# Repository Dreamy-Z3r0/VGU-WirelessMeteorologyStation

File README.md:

# VGU-WirelessMeteorologyStation

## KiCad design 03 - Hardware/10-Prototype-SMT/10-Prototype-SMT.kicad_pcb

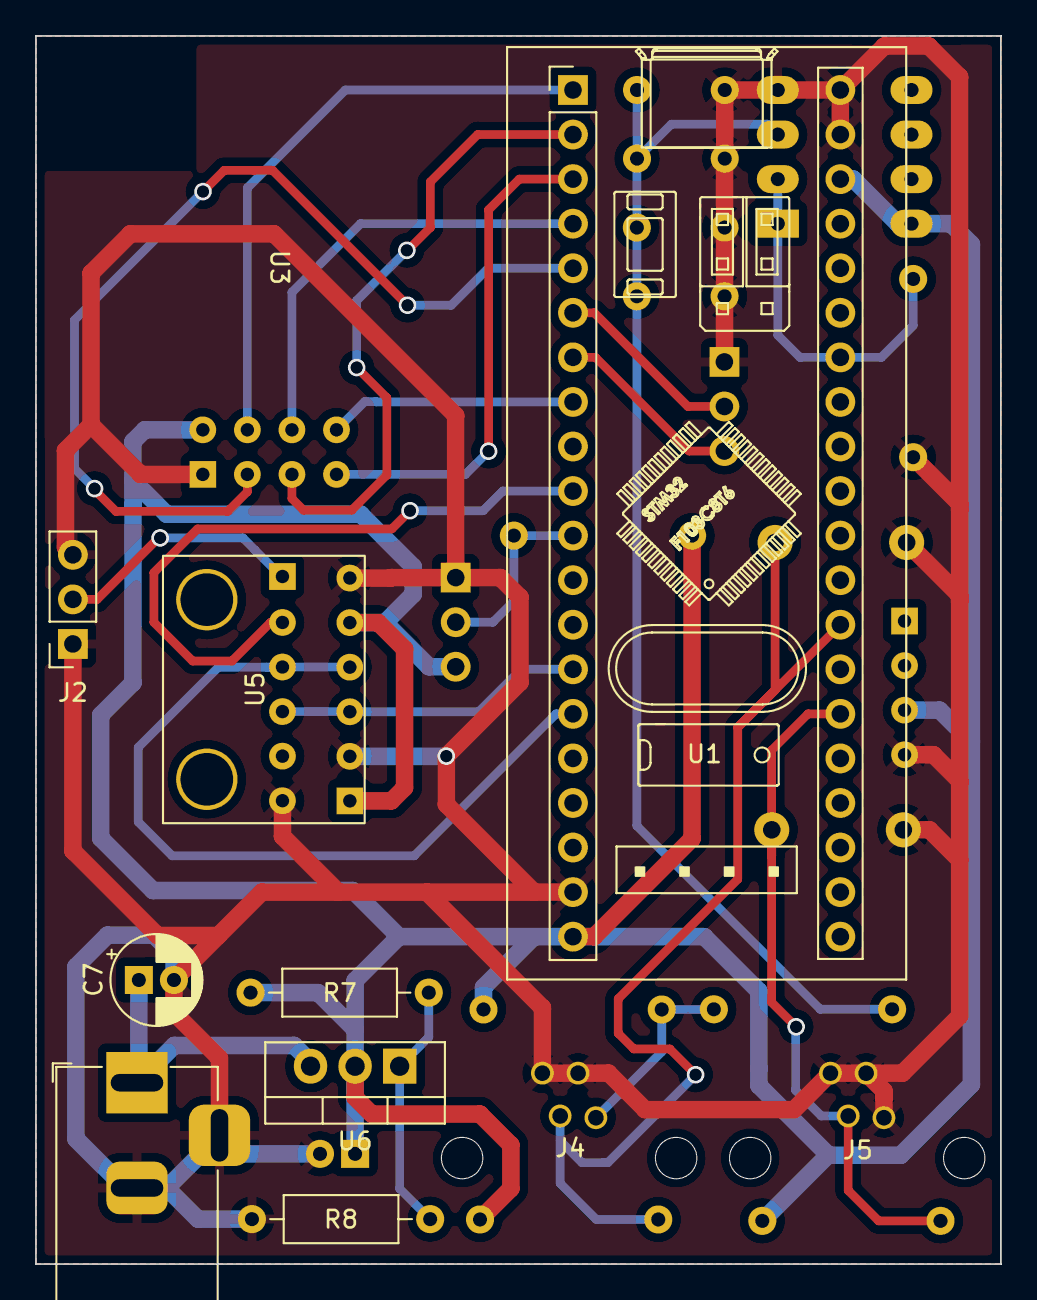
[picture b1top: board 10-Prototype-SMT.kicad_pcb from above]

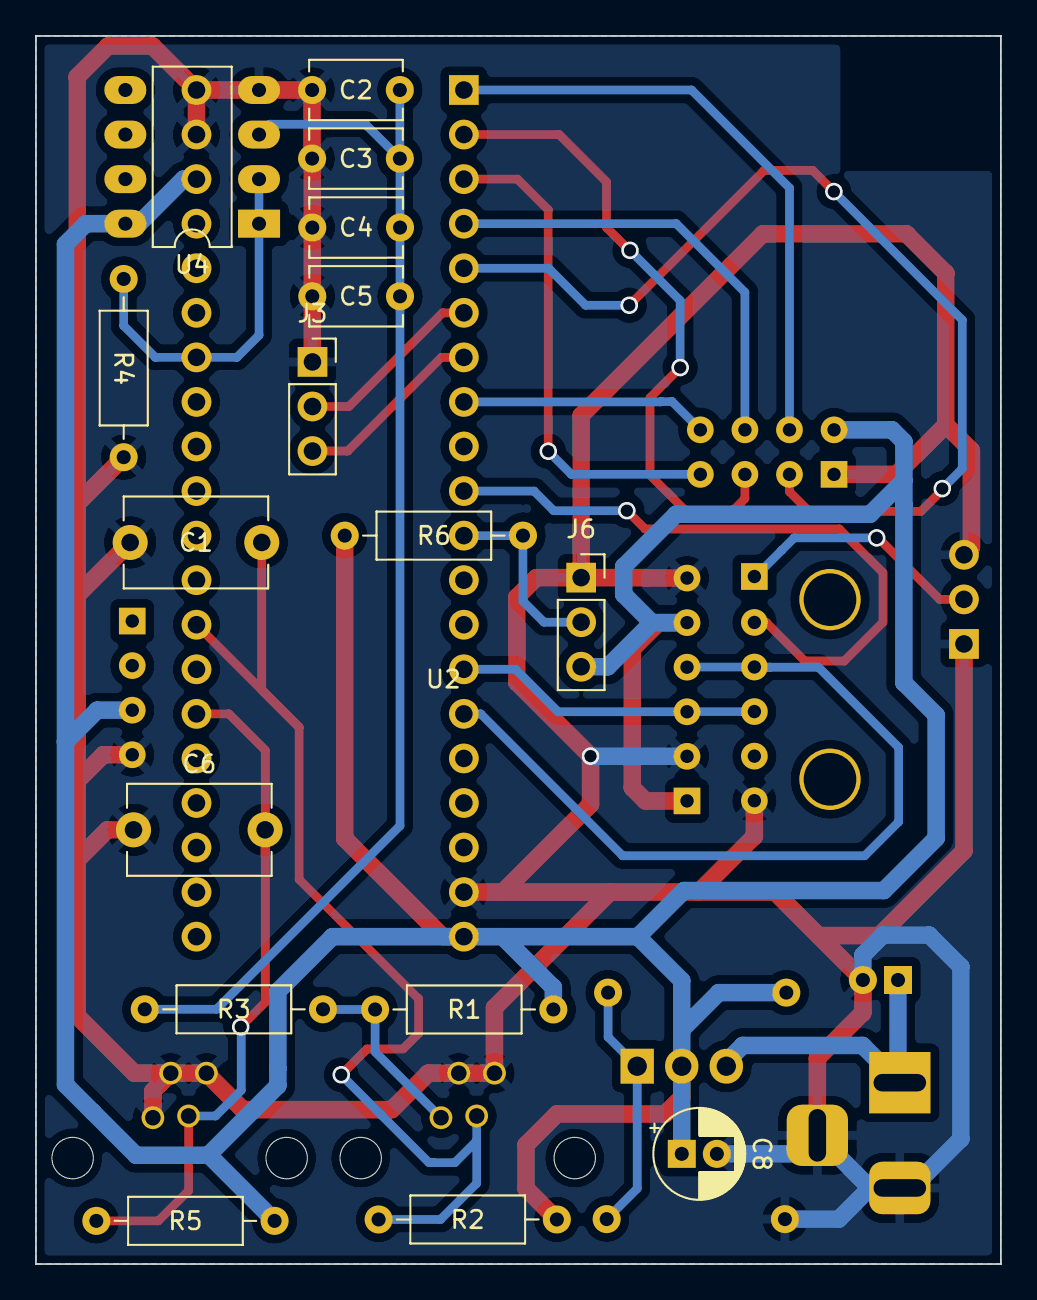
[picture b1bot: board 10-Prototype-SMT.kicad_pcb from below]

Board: 2 copper layers, 55.0 x 70.0 mm, 28 parts (17 on the bottom side), 22 nets.

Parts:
C1, C6: 68n; C_Disc_D8.0mm_W5.0mm_P7.50mm
C2: 10n; C_Disc_D5.1mm_W3.2mm_P5.00mm
C3: 4.7n; C_Disc_D5.1mm_W3.2mm_P5.00mm
C4: 3.3n; C_Disc_D5.1mm_W3.2mm_P5.00mm
C5: 2.2n; C_Disc_D5.1mm_W3.2mm_P5.00mm
C7: 0.1u; CP_Radial_D5.0mm_P2.00mm
C8: 1u; CP_Radial_D5.0mm_P2.00mm
J1: Barrel_Jack; BarrelJack_Horizontal
J2, J3, J6: Conn_01x03_Male; PinSocket_1x03_P2.54mm_Vertical
J4, J5: 4P4C
R1: 3k; R_Axial_DIN0207_L6.3mm_D2.5mm_P10.16mm_Horizontal
R2, R5: 33k; R_Axial_DIN0207_L6.3mm_D2.5mm_P10.16mm_Horizontal
R3: 680; R_Axial_DIN0207_L6.3mm_D2.5mm_P10.16mm_Horizontal
R4: 3.3k; R_Axial_DIN0207_L6.3mm_D2.5mm_P10.16mm_Horizontal
R6: 4.7k; R_Axial_DIN0207_L6.3mm_D2.5mm_P10.16mm_Horizontal
R7: 240; R_Axial_DIN0207_L6.3mm_D2.5mm_P10.16mm_Horizontal
R8: 390; R_Axial_DIN0207_L6.3mm_D2.5mm_P10.16mm_Horizontal
U1: YAAJ_BluePill; YAAJ_BluePill_1
U2: DS3231_Full_Pinout; DS3231_Module_FullSize
U3: SX1278_Minimal
U4: MCP6002-xP; DIP-8_W7.62mm_LongPads
U5: BME280_I2C_New_LK888; BME280_I2C_Small
U6: LM317_TO-220; TO-220-3_Vertical

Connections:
+3V3: C8.1, J6.3, R1.1, R2.1, R5.1, R6.1, R7.2, U1.20 (3V3), U1.38 (3V3), U2.3 (VCC), U3.2 (VCC), U4.8 (V+), U5.1 (VCC), U6.2 (VO)
/32768Hz out: J2.2, U2.5 (32K)
/Passive LPF: C2.1, C3.1, C4.1, C5.1, R3.2, U4.3 (+)
/V_adj: R7.1, R8.1, U6.1 (ADJ)
Anemometer: C1.2, J4.3, R2.2, U1.28 (PA3)
DS18B20: J6.2, R6.2, U1.11 (PB3)
GND: C1.1, C2.2, C3.2, C4.2, C5.2, C6.1, C7.2, C8.2, J1.2, J1.3, J2.1, J2.3, J3.1, J4.1, J4.2, J5.1, J5.2, J5.4, J6.1, R4.1, R8.2, U1.19 (GND), U1.39 (GND), U1.40 (GND), U2.4 (GND), U2.10 (GND), U3.1 (GND), U4.4 (V-), U5.2 (GND), U5.5 (ADDR)
I2C_CLK: U1.14 (PB6), U2.7 (SCL), U5.3 (SCL)
I2C_SDA: U1.15 (PB7), U2.8 (SDA), U5.4 (SDA)
LoRa_DIO0: U1.8 (PA11), U3.8 (DIO0)
LoRa_MISO: U1.3 (PB14), U3.7 (MISO)
LoRa_MOSI: U1.4 (PB15), U3.6 (MOSI)
LoRa_NCSS: U1.1 (PB12), U3.4 (NCSS)
LoRa_Reset: U1.5 (PA8), U3.3 (RST)
LoRa_SCLK: U1.2 (PB13), U3.5 (SCLK)
RTC_ALARM: U1.10 (PA15), U2.6 (SQW)
Rain_Gauge: C6.2, J5.3, R5.2, U1.26 (PA1)
UART_RX: J3.3, U1.7 (PA10)
UART_TX: J3.2, U1.6 (PA9)
VCC: C7.1, J1.1, U6.3 (VI)
WindVane_raw: J4.4, R1.2, R3.1
Wind_Vane: R4.2, U1.34 (PB1), U4.1, U4.2 (-)

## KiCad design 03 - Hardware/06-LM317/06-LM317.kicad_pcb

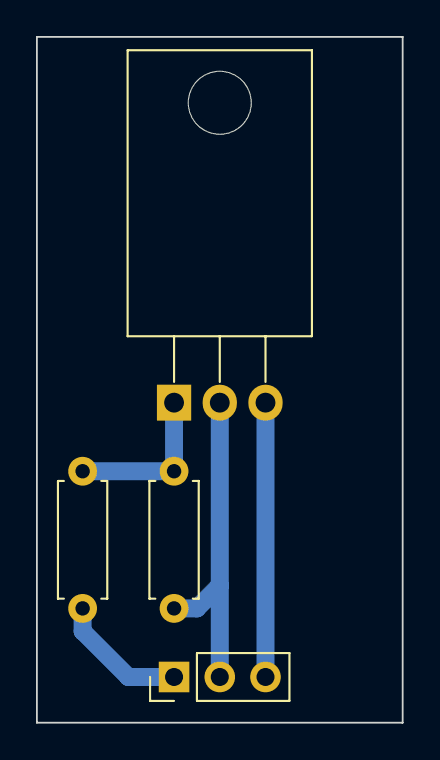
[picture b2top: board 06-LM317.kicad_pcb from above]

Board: 2 copper layers, 20.3 x 38.1 mm, 4 parts (0 on the bottom side), 4 nets.

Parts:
J1: Conn_01x03_Male; PinHeader_1x03_P2.54mm_Vertical
R1: 240; R_Axial_DIN0207_L6.3mm_D2.5mm_P7.62mm_Horizontal
R2: 390; R_Axial_DIN0207_L6.3mm_D2.5mm_P7.62mm_Horizontal
U1: LM317_TO-220; TO-220-3_Horizontal_TabDown

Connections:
/ADJ: R1.2, R2.1, U1.1 (ADJ)
GND: J1.1, R2.2
VIN: J1.3, U1.3 (VI)
VOUT: J1.2, R1.1, U1.2 (VO)

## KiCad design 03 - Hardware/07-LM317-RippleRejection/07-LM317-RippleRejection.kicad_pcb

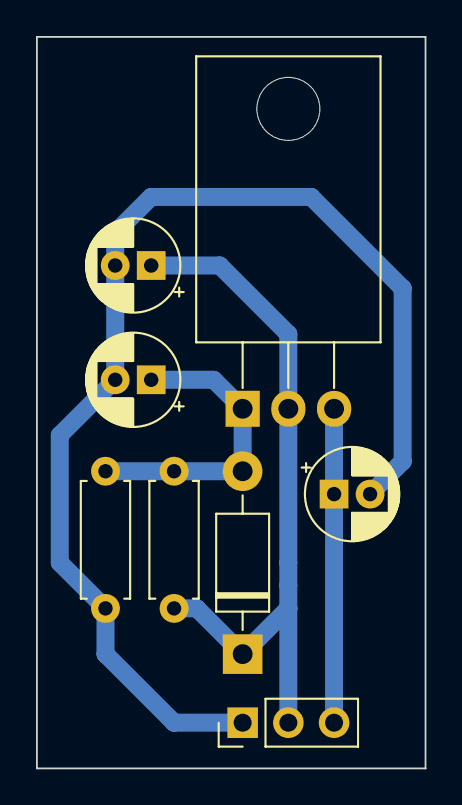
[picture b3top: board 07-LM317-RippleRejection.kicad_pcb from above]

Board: 2 copper layers, 21.6 x 40.6 mm, 8 parts (0 on the bottom side), 4 nets.

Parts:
C1: 0.1u; CP_Radial_D5.0mm_P2.00mm
C2: 10u; CP_Radial_D5.0mm_P2.00mm
C3: 1u; CP_Radial_D5.0mm_P2.00mm
D1: 1N4007; D_DO-41_SOD81_P10.16mm_Horizontal
J1: Conn_01x03_Male; PinHeader_1x03_P2.54mm_Vertical
R1: 240; R_Axial_DIN0207_L6.3mm_D2.5mm_P7.62mm_Horizontal
R2: 390; R_Axial_DIN0207_L6.3mm_D2.5mm_P7.62mm_Horizontal
U1: LM317_TO-220; TO-220-3_Horizontal_TabDown

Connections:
/ADJ: C2.1, D1.2 (A), R1.2, R2.1, U1.1 (ADJ)
GND: C1.2, C2.2, C3.2, J1.1, R2.2
VIN: C1.1, J1.3, U1.3 (VI)
VOUT: C3.1, D1.1 (K), J1.2, R1.1, U1.2 (VO)

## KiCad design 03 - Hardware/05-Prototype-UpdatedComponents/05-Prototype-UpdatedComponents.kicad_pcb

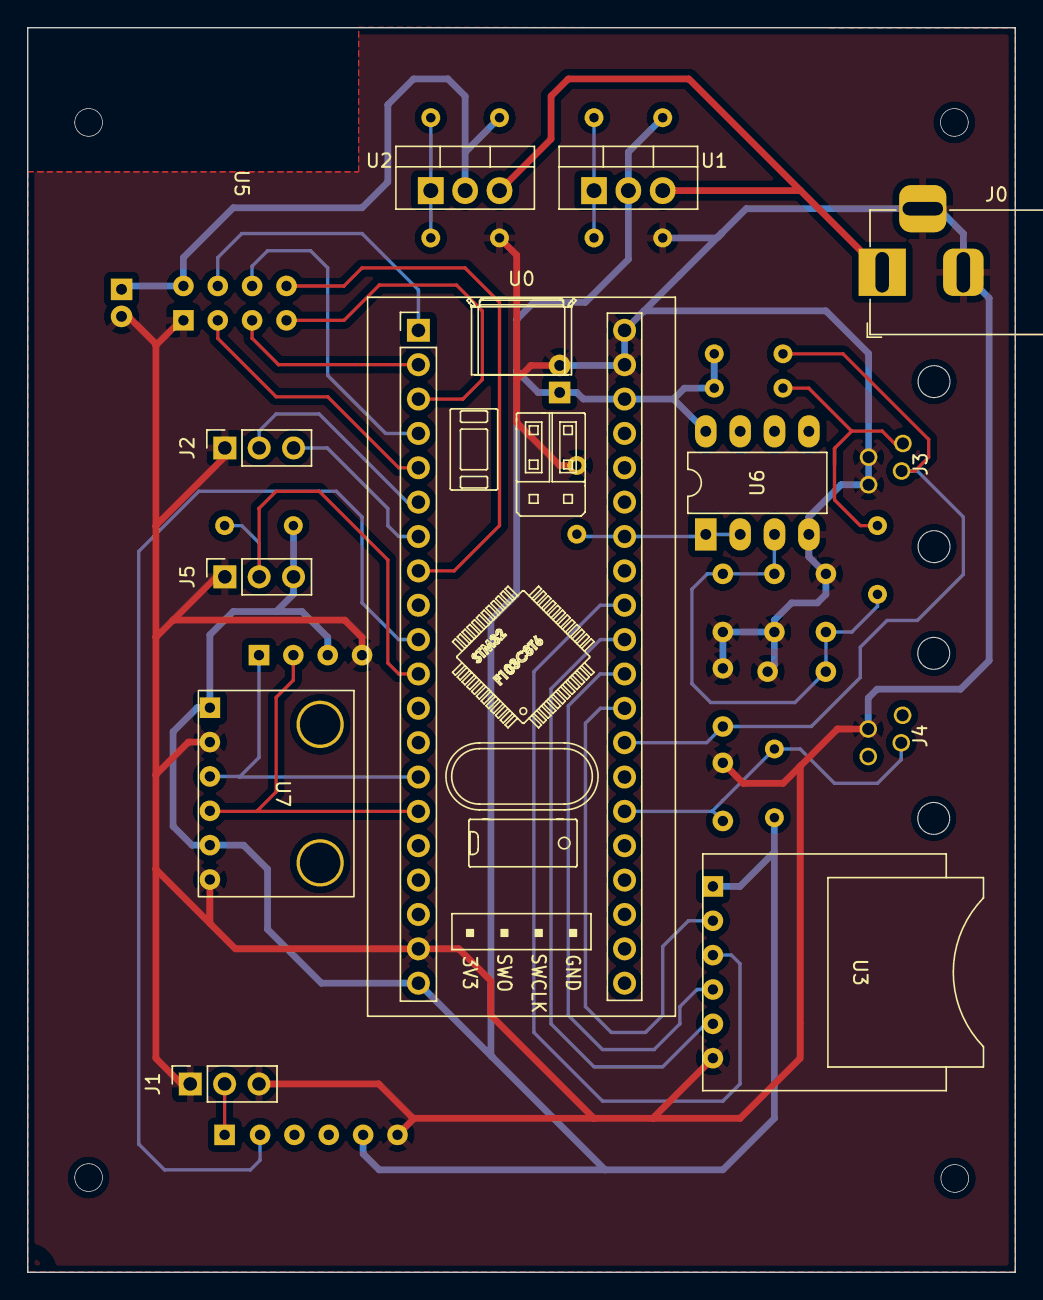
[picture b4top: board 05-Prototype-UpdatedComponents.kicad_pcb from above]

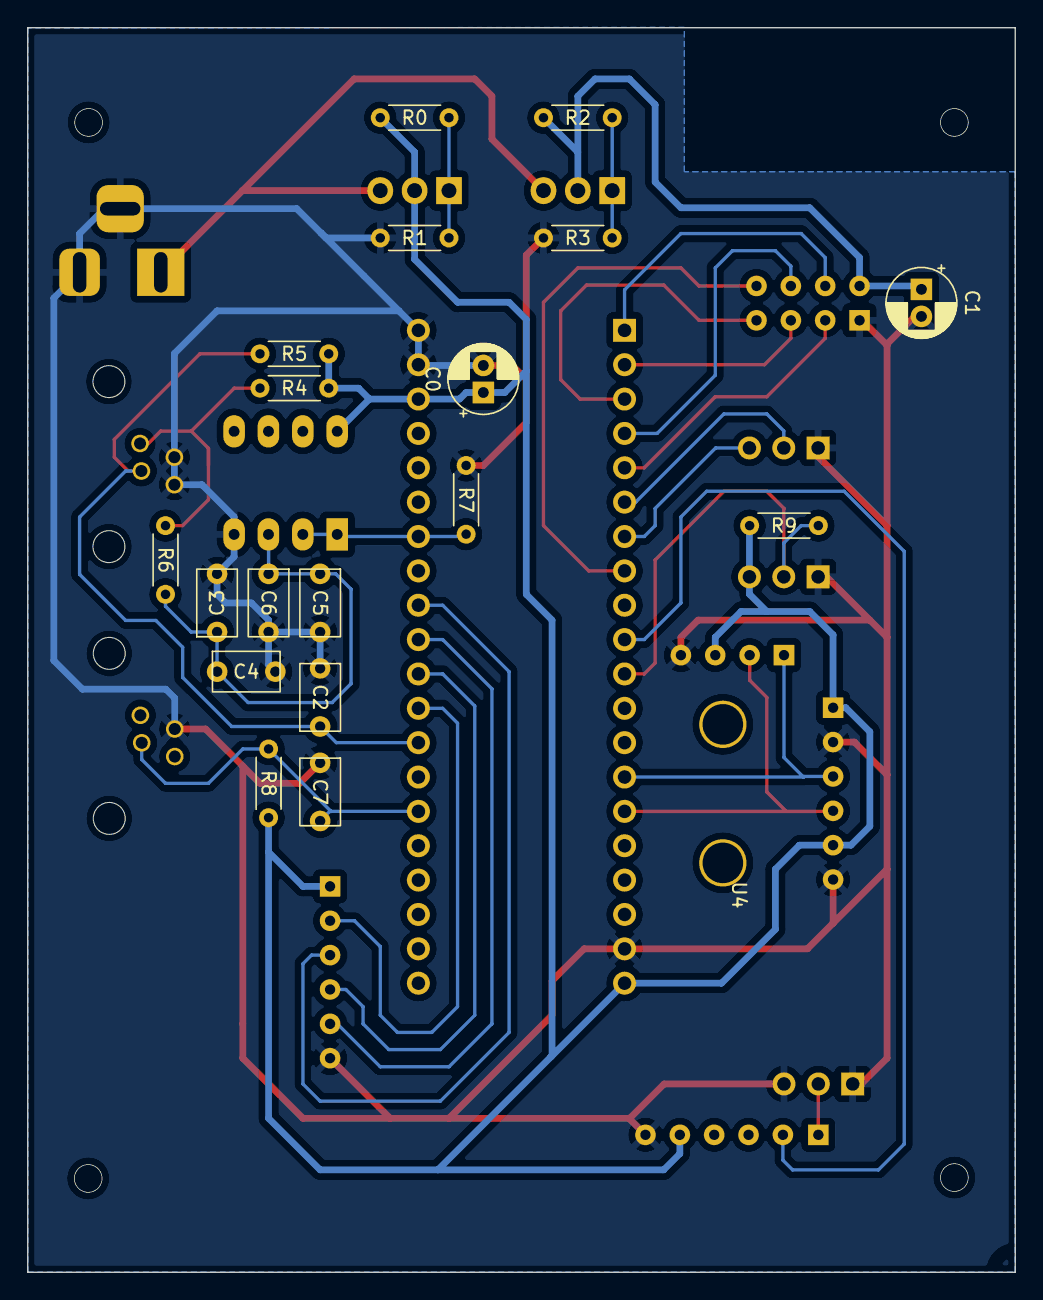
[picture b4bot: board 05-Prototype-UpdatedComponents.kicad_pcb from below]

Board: 2 copper layers, 73.0 x 92.0 mm, 32 parts (19 on the bottom side), 28 nets.

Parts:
C0, C1: 1u; CP_Radial_D5.0mm_P2.00mm
C2, C7: 68n; C_Radial_W5.5mm_H9.0mm_T3.0mm_P4.3mm
C3: 10n; C_Radial_W5.5mm_H9.0mm_T3.0mm_P4.3mm
C4: 4.7n; C_Radial_W5.5mm_H9.0mm_T3.0mm_P4.3mm
C5: 3.3n; C_Radial_W5.5mm_H9.0mm_T3.0mm_P4.3mm
C6: 2.2n; C_Radial_W5.5mm_H9.0mm_T3.0mm_P4.3mm
J0: Barrel_Jack; BarrelJack_Horizontal
J1, J2, J5: Conn_01x03_Male; PinSocket_1x03_P2.54mm_Vertical
J3, J4: 4P4C
R0, R2: 240; R_Axial_DIN0204_L3.6mm_D1.6mm_P5.08mm_Horizontal
R1, R3: 390; R_Axial_DIN0204_L3.6mm_D1.6mm_P5.08mm_Horizontal
R4, R7: 3.3k; R_Axial_DIN0204_L3.6mm_D1.6mm_P5.08mm_Horizontal
R5, R8: 33k; R_Axial_DIN0204_L3.6mm_D1.6mm_P5.08mm_Horizontal
R6: 680; R_Axial_DIN0204_L3.6mm_D1.6mm_P5.08mm_Horizontal
R9: 4.7k; R_Axial_DIN0204_L3.6mm_D1.6mm_P5.08mm_Horizontal
U0: YAAJ_BluePill; YAAJ_BluePill_1
U1, U2: LM317_TO-220; TO-220-3_Vertical
U3: microSD_Module_3V3_Horizontal; microSD_mini
U4: DS3231_Module_FullAccess; DS3231_Module_FullSize
U5: SX1278_Minimal
U6: MCP6002-xP; DIP-8_W7.62mm_LongPads
U7: BME280_I2C_New_LK888; BME280_I2C_Small

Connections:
+3.3VP: C1.1, R2.1, U2.2 (VO), U5.2 (VCC)
+3V3: C0.1, J5.3, R0.1, R4.1, R5.1, R8.1, R9.1, U0.20 (3V3), U0.38 (3V3), U1.2 (VO), U3.1 (3V3), U4.3 (VCC), U6.8 (V+), U7.1 (VCC)
+VDC: J0.1, U1.3 (VI), U2.3 (VI)
/32768Hz out: J1.2, U4.5 (32K)
/Passive LPF: C3.1, C4.1, C5.1, C6.1, R6.2, U6.3 (+)
/V_adj: R0.2, R1.1, U1.1 (ADJ)
/V_adj_VP: R2.2, R3.1, U2.1 (ADJ)
Anemometer: C2.2, J3.3, R5.2, U0.28 (PA3)
DS18B20: J5.2, R9.2, U0.11 (PB3)
GND: C0.2, C1.2, C2.1, C3.2, C4.2, C5.2, C6.2, C7.1, J0.2, J0.3, J1.1, J1.3, J2.1, J3.1, J3.2, J4.2, J5.1, R1.2, R3.2, R7.1, U0.19 (GND), U0.39 (GND), U0.40 (GND), U3.6 (GND), U4.4 (GND), U5.1 (GND), U6.4 (V-), U7.2 (GND), U7.5 (ADDR)
I2C_CLK: U0.14 (PB6), U4.1 (SCL), U7.3 (SCL)
I2C_SDA: U0.15 (PB7), U4.2 (SDA), U7.4 (SDA)
LoRa_DIO0: U0.8 (PA11), U5.8 (DIO0)
LoRa_MISO: U0.3 (PB14), U5.7 (MISO)
LoRa_MOSI: U0.4 (PB15), U5.6 (MOSI)
LoRa_NCSS: U0.1 (PB12), U5.4 (NCSS)
LoRa_Reset: U0.5 (PA8), U5.3 (RST)
LoRa_SCLK: U0.2 (PB13), U5.5 (SCLK)
MICROSD_NCSS: U0.29 (PA4), U3.2 (CS)
RTC_ALARM: U0.10 (PA15), U4.6 (SQW)
Rain gauge: C7.2, J4.3, R8.2, U0.26 (PA1)
SPI1_MISO: U0.31 (PA6), U3.5 (MISO)
SPI1_MOSI: U0.32 (PA7), U3.3 (MOSI)
SPI1_SCK: U0.30 (PA5), U3.4 (CLK)
UART_RX: J2.3, U0.7 (PA10)
UART_TX: J2.2, U0.6 (PA9)
WindVane_filtered: R7.2, U0.34 (PB1), U6.1, U6.2 (-)
WindVane_raw: J3.4, R4.2, R6.1

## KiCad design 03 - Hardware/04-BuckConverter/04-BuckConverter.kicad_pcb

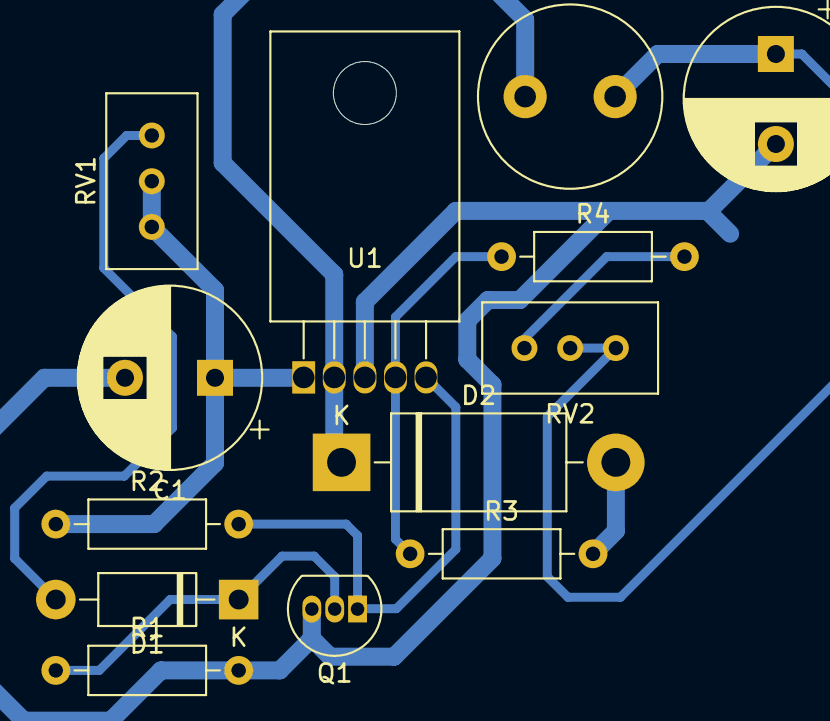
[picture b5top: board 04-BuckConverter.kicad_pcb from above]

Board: 2 copper layers, 13 parts (0 on the bottom side), 9 nets.

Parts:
C1: 470u; CP_Radial_D10.0mm_P5.00mm
C2: 220n; CP_Radial_D10.0mm_P5.00mm
D1: 1N47xxA; D_DO-41_SOD81_P10.16mm_Horizontal
D2: SR540; D_DO-201AD_P15.24mm_Horizontal
L1: 68u; L_Radial_D10.0mm_P5.00mm_Neosid_SD12k_style3
Q1: BC548; TO-92_Inline
R1, R2: 47k; R_Axial_DIN0207_L6.3mm_D2.5mm_P10.16mm_Horizontal
R3, R4: 1k; R_Axial_DIN0207_L6.3mm_D2.5mm_P10.16mm_Horizontal
RV1, RV2: 1k; Potentiometer_Bourns_3296W_Vertical
U1: LM2596-ADJ; LM2596-ADJ-Horizontal-THT

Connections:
Earth: C1.2, C2.2, D2.2 (A), Q1.3 (E), R1.2, R3.2, U1.3 (GND)
unnamed: D1.1 (K), Q1.2 (B), R1.1
unnamed: D1.2 (A), RV1.1
unnamed: D2.1 (K), L1.1, U1.2 (OUT)
unnamed: C2.1, L1.2, RV2.2, RV2.3
unnamed: R3.1, R4.1, U1.4 (FB)
unnamed: R4.2, RV2.1
unnamed: C1.1, R2.1, RV1.2, RV1.3, U1.1 (VIN)
unnamed: Q1.1 (C), R2.2, U1.5 (~ON/OFF)

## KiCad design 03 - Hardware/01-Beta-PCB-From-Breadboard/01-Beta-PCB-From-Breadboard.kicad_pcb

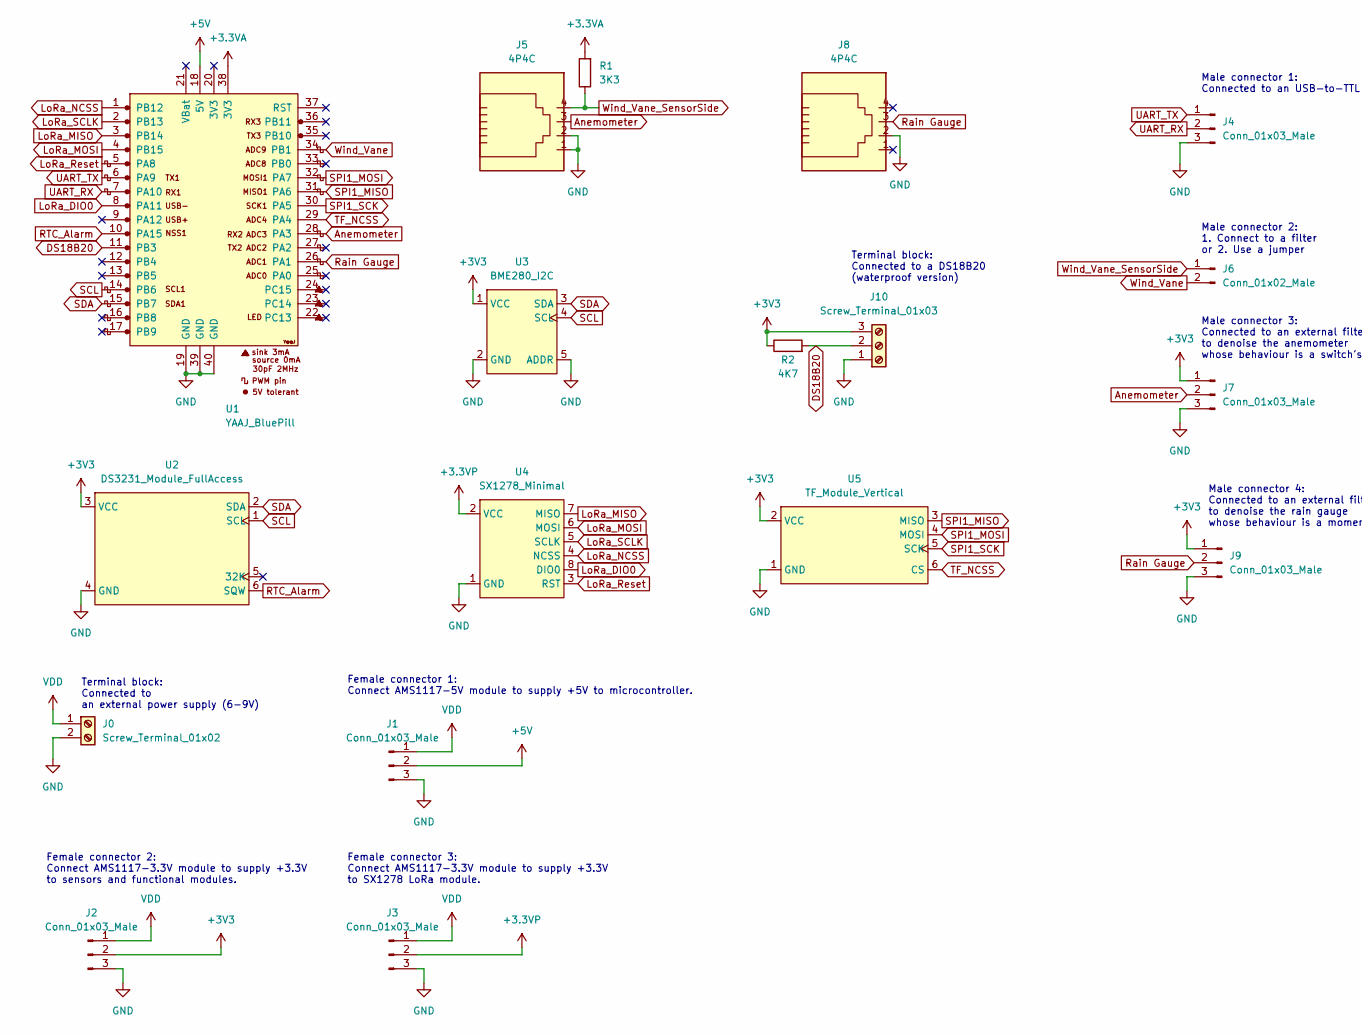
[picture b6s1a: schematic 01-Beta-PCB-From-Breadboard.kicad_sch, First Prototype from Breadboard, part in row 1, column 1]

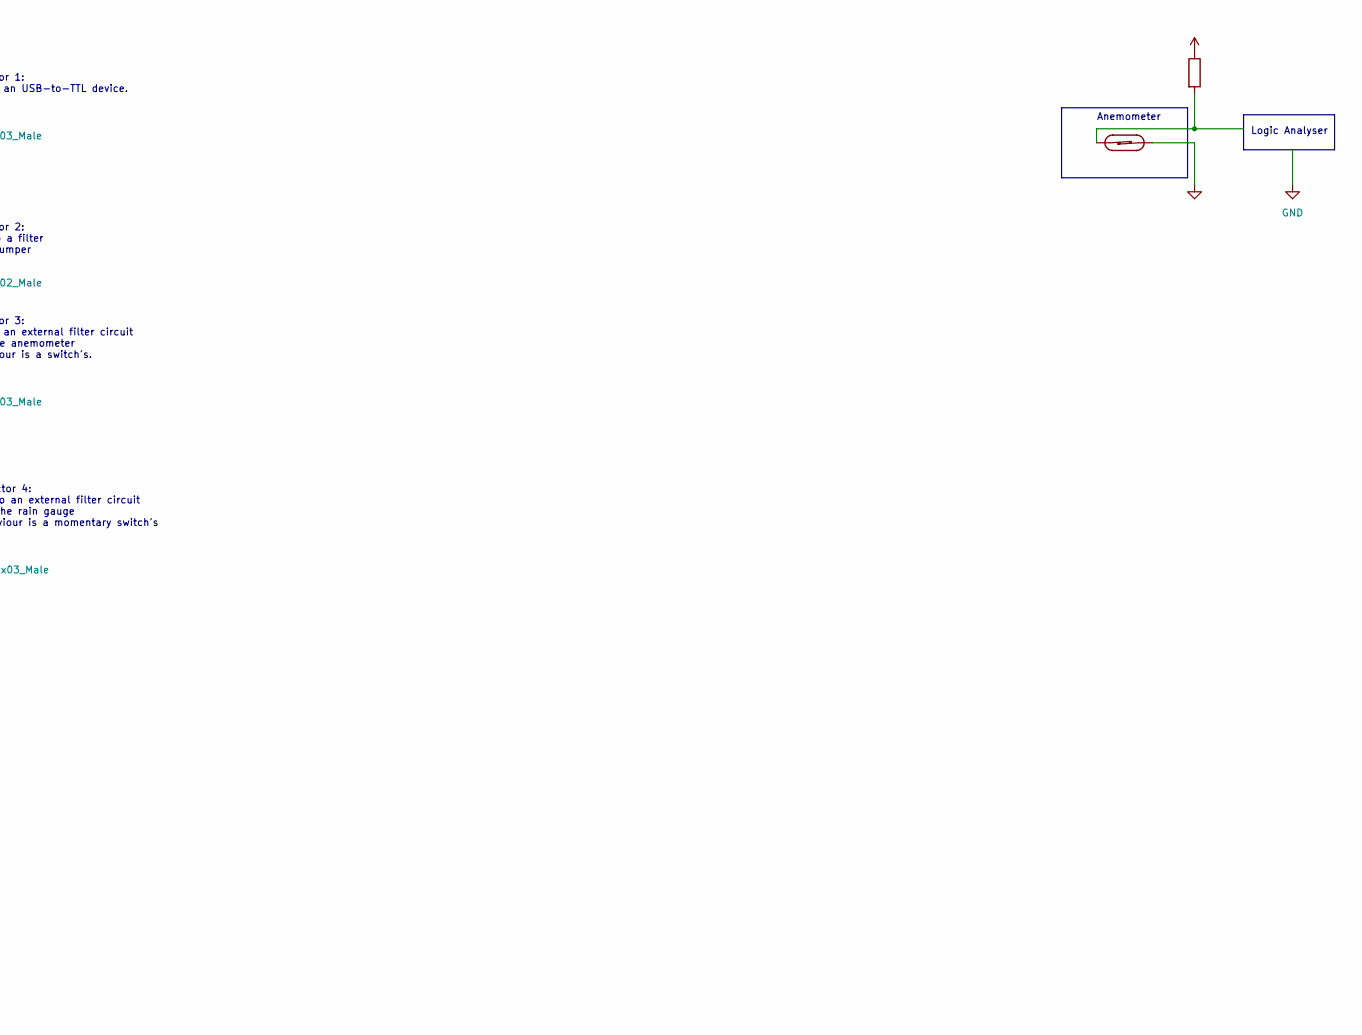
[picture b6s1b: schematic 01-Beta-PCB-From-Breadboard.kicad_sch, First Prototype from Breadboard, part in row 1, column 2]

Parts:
J0: Screw_Terminal_01x02; TerminalBlock_TE_282834-2_1x02_P2.54mm_Horizontal
J1, J2, J3, J4, J7, J9: Conn_01x03_Male; PinHeader_1x03_P2.54mm_Vertical
J5, J8: 4P4C
J6: Conn_01x02_Male; PinHeader_1x02_P2.54mm_Vertical
J10: Screw_Terminal_01x03; TerminalBlock_TE_282834-3_1x03_P2.54mm_Horizontal
R1: 3K3; R_Axial_DIN0207_L6.3mm_D2.5mm_P10.16mm_Horizontal
R2: 4K7; R_Axial_DIN0207_L6.3mm_D2.5mm_P10.16mm_Horizontal
U1: YAAJ_BluePill; YAAJ_BluePill_1
U2: DS3231_Module_FullAccess; DS3231_Module_Minimal
U3: BME280_I2C
U4: SX1278_Minimal
U5: TF_Module_Vertical; TF_Module_Veritcal

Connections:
+3.3VA: R1.2, U1.38 (3V3)
+3.3VP: J3.2, U4.2 (VCC)
+3V3: J2.2, J7.1, J9.1, J10.3, R2.1, U2.3 (VCC), U3.1 (VCC), U5.2 (VCC)
+5V: J1.2, U1.18 (5V)
Anemometer: J5.3, J7.2, U1.28 (PA3)
DS18B20: J10.2, R2.2, U1.11 (PB3)
GND: J0.2, J1.3, J2.3, J3.3, J4.3, J5.1, J5.2, J7.3, J8.2, J9.3, J10.1, U1.19 (GND), U1.39 (GND), U1.40 (GND), U2.4 (GND), U3.2 (GND), U3.5 (ADDR), U4.1 (GND), U5.1 (GND)
LoRa_DIO0: U1.8 (PA11), U4.8 (DIO0)
LoRa_MISO: U1.3 (PB14), U4.7 (MISO)
LoRa_MOSI: U1.4 (PB15), U4.6 (MOSI)
LoRa_NCSS: U1.1 (PB12), U4.4 (NCSS)
LoRa_Reset: U1.5 (PA8), U4.3 (RST)
LoRa_SCLK: U1.2 (PB13), U4.5 (SCLK)
RTC_Alarm: U1.10 (PA15), U2.6 (SQW)
Rain Gauge: J8.3, J9.2, U1.26 (PA1)
SCL: U1.14 (PB6), U2.1 (SCL), U3.4 (SCL)
SDA: U1.15 (PB7), U2.2 (SDA), U3.3 (SDA)
SPI1_MISO: U1.31 (PA6), U5.3 (MISO)
SPI1_MOSI: U1.32 (PA7), U5.4 (MOSI)
SPI1_SCK: U1.30 (PA5), U5.5 (SCK)
TF_NCSS: U1.29 (PA4), U5.6 (CS)
UART_RX: J4.2, U1.7 (PA10)
UART_TX: J4.1, U1.6 (PA9)
VDD: J0.1, J1.1, J2.1, J3.1
Wind_Vane: J6.2, U1.34 (PB1)
Wind_Vane_SensorSide: J5.4, J6.1, R1.1

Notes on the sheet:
Anemometer
Male connector 2: 1. Connect to a filter or 2. Use a jumper
Female connector 2: Connect AMS1117-3.3V module to supply +3.3V to sensors and functional modules.
Terminal block: Connected to an external power supply (6-9V)
Male connector 3: Connected to an external filter circuit to denoise the anemometer whose behaviour is a switch's.
Male connector 4: Connected to an external filter circuit to denoise the rain gauge whose behaviour is a momentary switch's
Male connector 1: Connected to an USB-to-TTL device.
Terminal block: Connected to a DS18B20 (waterproof version)
Logic Analyser
Female connector 3: Connect AMS1117-3.3V module to supply +3.3V to SX1278 LoRa module.
Female connector 1: Connect AMS1117-5V module to supply +5V to microcontroller.

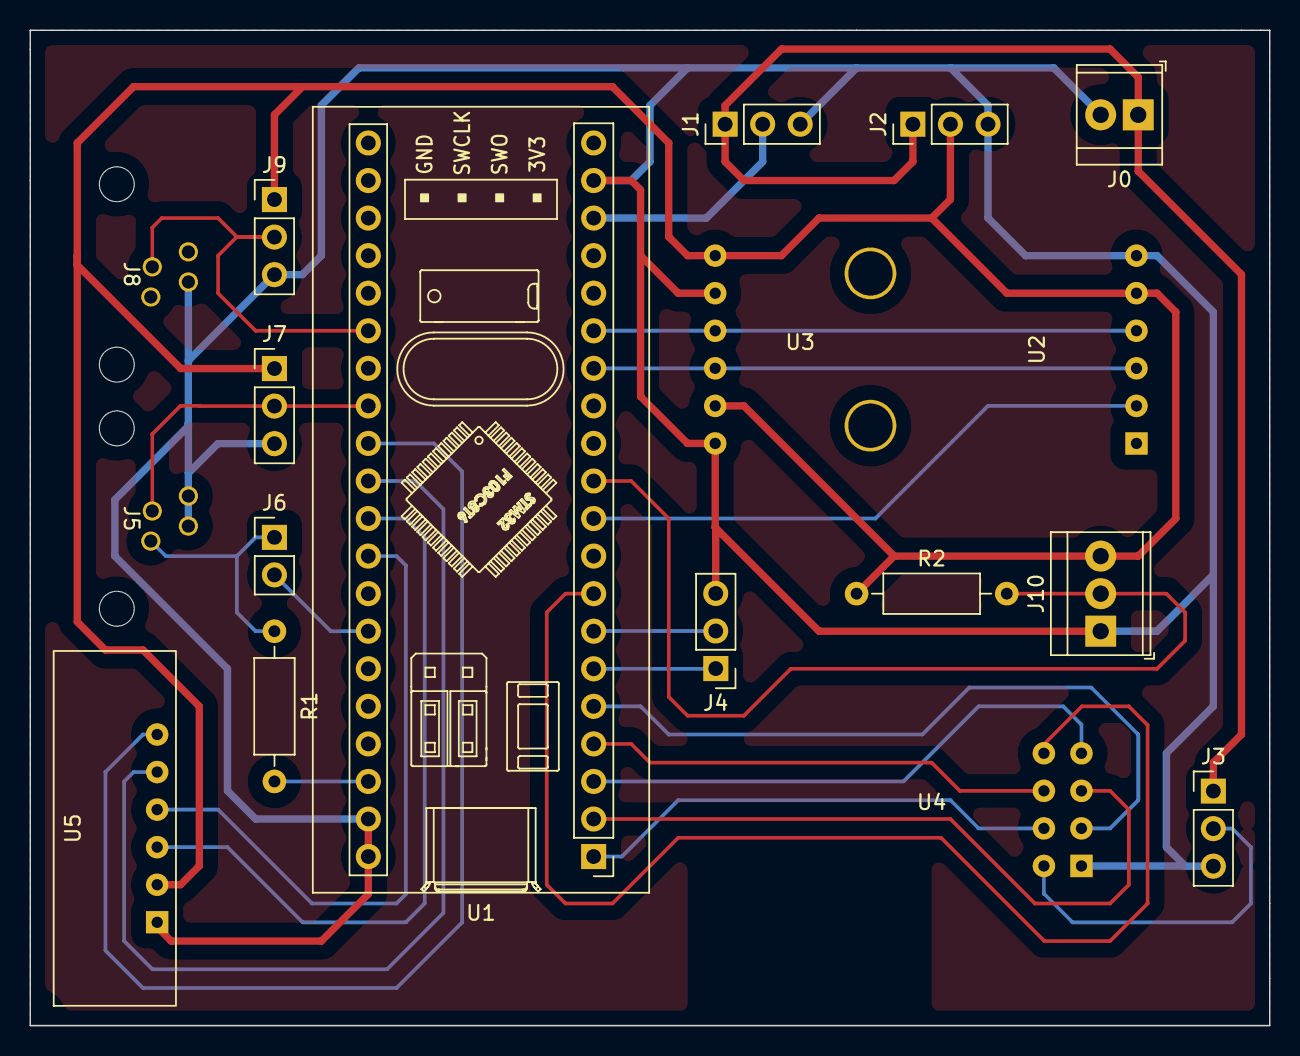
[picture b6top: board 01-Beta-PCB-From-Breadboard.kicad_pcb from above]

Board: 2 copper layers, 83.8 x 67.3 mm, 18 parts (0 on the bottom side), 26 nets.

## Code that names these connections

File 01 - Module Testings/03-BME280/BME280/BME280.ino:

/******************************************************************
 ******************************************************************
 ***    BME280 test for STM32F103CBT6 on Arduino framework      ***
 *** ---------------------------------------------------------- ***
 ***                                                            ***
 *** BME280 is a temperature - humidity - barometric pressure   ***
 *** sensor which could communicate via either I2C or SPI. This ***
 *** test is designed for the default SPI on the STM32.         ***
 ***                                                            ***
 *** On the STM32F103CBT6, the default SPI is mapped to SPI1:   ***
 *** (MOSI, MISO, SCK, NCSS) = (PA7, PA6, PA5, PA4). The NCSS   ***
 *** pin, however, is user-defined in the code.                 ***
 ***                                                            ***
 *** Should other configurations be desired, the followings     ***
 *** could be applied:                                          ***
 ***  - Interface:                                              ***
 ***    + I2C: Adafruit_BME280 bme;                             ***                                                            
 ***    + Default hardware SPI1: Adafruit_BME280 bme(BME_CS);   ***                                                            
 ***    + Software SPI: Adafruit_BME280 bme(BME_CS, BME_MOSI,   ***                                                            
 ***                                        BME_MISO, BME_SCK); ***    
 ***                                                            ***                                        
 *** - Configurations for I2C:                                  ***                                                            
 ***    + Default: bme.begin(); -> Also used for SPI            *** 
 ***    + Different address: bme.begin(ADDRESS);                ***                                                            
 ***    + Different I2C bus: bme.begin(Address, &Wire_x);       ***    
 ***                                                            ***    
 *** Note:                                                      ***                                                            
 ***  - I2C address could be either 0x77 or 0x76, thus no more  ***                                                            
 ***    than 2 BME280s on the same I2C bus.                     ***
 ***  - Wire_x is Wire1 for I2C1, Wire2 for I2C2, etc.          ***
 ***  - Any free digital pins could be used as BME_CS for SPI,  ***                                                        
 ***    so the maximum allowed number of BME280s on the same    ***  
 ***    SPI bus is the number of free digital pins.             ***    
 ******************************************************************
 ******************************************************************/


#include <SPI.h>
#include <Adafruit_Sensor.h>
#include <Adafruit_BME280.h>

// The following comments are for the purpose of remapping SPI only, which is no longer of use.
//#define default_MOSI_Pin PB15
//#define default_MISO_Pin PB14
//#define default_SCLK_Pin PB13
//#define default_SSEL_Pin PB12

#define BME_CS PA4
#define SEALEVELPRESSURE_HPA (1013.25)

Adafruit_BME280 bme(BME_CS); // hardware SPI

typedef struct {
  float temperature;
  float humidity;
  float pressure;
} BME280_Data;

BME280_Data BME280_dataStorage;
bool BME280_readFlag = false;

void setup() {
  Serial.begin(9600);

//  SPI.setMOSI(default_MOSI_Pin);
//  SPI.setMISO(default_MISO_Pin);
//  SPI.setSCLK(default_SCLK_Pin);
//  SPI.setSSEL(default_SSEL_Pin);

  unsigned status;
  status = bme.begin();
  if (!status) {
    while (1);
  }

  HardwareTimer *sensorRoutine = new HardwareTimer(TIM4);
  sensorRoutine->setOverflow(1, HERTZ_FORMAT);
  sensorRoutine->attachInterrupt(std::bind(read_BME280, &BME280_dataStorage, &BME280_readFlag));
  sensorRoutine->resume();
}

void loop() {
  if (BME280_readFlag) {
    BME280_readFlag = false;

    Serial.print("Ambient temperature = ");
    Serial.print(BME280_dataStorage.temperature);
    Serial.println(" ºC");

    Serial.print("Relative humidity = ");
    Serial.print(BME280_dataStorage.humidity);
    Serial.println(" %RH");

    Serial.print("Atmospheric pressure = ");
    Serial.print(BME280_dataStorage.pressure);
    Serial.println(" hPa");

    Serial.println();
  }
}

void read_BME280(BME280_Data* storage, bool* controlFlag) {
  storage->temperature = bme.readTemperature();         // Read temperature data in degree Celsius
  storage->pressure    = bme.readPressure() / 100.0F;   // Read barometric data in hPa
  storage->humidity    = bme.readHumidity();            // Read relative humidity data in %RH

  *controlFlag = true;
}

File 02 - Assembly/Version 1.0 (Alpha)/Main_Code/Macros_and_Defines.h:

#include "Libraries.h"


/****************************
 *** Basic communications ***
 ****************************/
// UART
#define DEBUGGING_OVER_SERIAL   // Un-comment to enable printing over Serial / Comment to disable printing over Serial

#ifdef DEBUGGING_OVER_SERIAL
#define BAUD_RATE 9600          // Define baud rate for Serial monitor
#endif

bool newLine = false;


/********************************
 *** SD card's requirement(s) ***
 ********************************/
//#define SD_CS_Pin default_SSEL_Pin


/*******************************
 *** DS32331 Real-time Clock ***
 *******************************/
#define Alarm_InputPin PB12
DS3231_Control RTC_DS3231;


/*******************************************************************
 *** BME280: Temperature - Humidity - Barometric pressure sensor ***
 *******************************************************************/
#define BME_CS_Pin PA4    // SSEL pin for BME280

Adafruit_BME280 bme280(BME_CS_Pin);    // Create an instance to use libraries for BME280
BME280_Control BME280_Device(&bme280);


/***********************************
 *** DS18B20: Temperature sensor ***
 ***********************************/
#define OneWireBus PB3    // Digital pin as the one-wire bus
DS18B20_Control DS18B20_Device(OneWireBus);


/******************
 *** Rain gauge ***
 ******************/
#define RainGauge_InputPin PA1
Precipitation RainGauge;


/*****************
 *** Wind vane ***
 *****************/
#define WindVane_InputPin PB1
WindVane_Control WindVane(WindVane_InputPin);


/******************
 *** Anemometer ***
 ******************/
#define Anemometer_InputPin PA3
Anemometer_Control Anemometer_Device(Anemometer_InputPin);

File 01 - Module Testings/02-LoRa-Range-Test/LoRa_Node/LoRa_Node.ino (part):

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 ***      Hardware connections
 ***  STM32  | SX1278 |  Function
 *** --------|--------|----------------
 ***   PB15  |  MOSI  | MOSI
 ***   PB14  |  MISO  | MISO
 ***   PB13  |  SCK   | CLK
 ***   PB12  |  NSS   | CS0
 *** --------|--------|----------------
 ***   PA8   |  RST   | LoRa Reset
 ***   PA11  |  DIO0  | EXTI from LoRa
 */


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
#define LED_INDICATOR PC13

#define SPI2_MOSI_Pin PB15   // SPI2 MOSI pin
#define SPI2_MISO_Pin PB14   // SPI2 MISO pin
#define SPI2_SCLK_Pin PB13   // SPI2 SCLK pin
//#define SPI2_SSEL_Pin PB12   // SPI2 SSEL pin -> not used

SPIClass SPI_2(SPI2_MOSI_Pin, SPI2_MISO_Pin, SPI2_SCLK_Pin);

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
const long frequency = 433E6;   // LoRa frequency

const int csPin = PB12;    // SPI NCSS for LoRa
const int resetPin = PA8;  // LoRa reset
const int irqPin = PA11;   // Interrupt by LoRa

int spreadingFactor = 0;
long signalBandwidth = 0;
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
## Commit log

2022-06-29 Move files from separated repositories
2022-06-29 Move files from separate repositories (2)
2022-06-29 Initialisation
    Create and update header and source files for main code, LoRa, and BME280.
    To be done:
    1. Create and update header and source files for SD
    2. Handle inputs for BME280 settings and LoRa settings
    3. Test the code
2022-06-30 Update Multiple SPI - Multiple Slaves
2022-07-03 Add handlers
2022-07-05 Test new command formats
2022-07-05 Test new protocol
2022-07-05 Update string handler
2022-07-07 Finishing LoRa connectivity test
2022-07-07 Update commands
2022-07-08 Initialize range test
2022-07-12 Restructure connectivity tests and add new ones
2022-07-13 Modify LoRa library and update source codes
2022-07-14 Switching LoRa channels is now available
2022-07-14 Final touch on channel switching
2022-07-14 Further updates
2022-07-14 typos :/
2022-07-14 Tada! Let's start LoRa CAD test!
    (CAD: Channel Activity Detection)
2022-07-14 update CAD source code for tests
2022-07-16 anemometer
2022-07-17 update one of anemometer reading methods
2022-07-20 Remove CAD and update wind sensors' tests
2022-07-20 Rain gauge and alarm test codes
2022-07-21 Remove SPI remapping in version 0.3 beta
2022-07-22 Launch version 0.4 (beta)
2022-07-24 OOP style for version 0.1 -> version 0.0.1
2022-07-24 Minor update, version 0.2 -> 0.2.1
2022-07-24 OOP style for version 0.2 -> version 0.2.2
2022-07-24 Remove excessive codes
2022-07-25 OOP style for version 0.3 -> version 0.3.1
2022-07-25 OOP style of version 0.4 -> version 0.4.1
2022-07-28 ongoing codes
2022-07-29 update test files
2022-07-31 update ongoing
2022-08-08 update?
2022-08-08 just a comment :)
2022-08-09 add source code for anemometer
2022-08-11 Add anemometer test for non-blocking applications
2022-08-13 Rewrite new source code of version 0.6
2022-08-15 Re-arrange source code structures + resolve issues
2022-08-18 Initiate the first alpha release
2022-08-19 New test series with HAL; starting with Serial
2022-08-22 Reface README.md
2022-08-25 HAL Implementation for version 1.0 (Alpha)
2022-08-25 Update IIR filter
2022-08-31 Simplify data-processing routine for wind vane
2022-08-31 Inheritance
2022-08-31 Allow update of timestamps for sensors
2022-09-05 Add missing delete[] command + fix printf issues
2022-09-05 Remove unused (commented) codes
2022-09-05 Remove excessive file(s)
2022-09-05 First implementation of C++ class inheritance
2022-09-07 Rearrange code structure
2022-09-07 Inheritance for Anemometer_Control
2022-09-08 Inheritance update: Precipitation, BME280, DS18B20
2022-09-08 Rename file(s)
2022-09-08 Rearrange codes
2022-09-09 The start of general control class for sensors
2022-09-10 Updates regarding sensor general control class
2022-09-12 Further updates of Sensor_Control class
2022-09-12 New anemometer-reading method!!!
    New changes bring:
    1. Saving 1 hardware timer for future uses
    2. Less variables/flags to be managed
    3. Simplified codes
2022-09-12 Some new lines of code
2022-09-13 Revision needed; wind vane fails to read correctly
2022-09-14 Changed the order of IIR filter from 2nd to 1st
2022-09-14 add comments
2022-09-15 Rename files. Nothing else.
2022-09-15 New wind vane method. Update for README files.
2022-09-15 Initiate a new beta test
2022-09-15 Update outdated codes
2022-09-15 Add/Update timer callbacks
2022-09-16 Add new control variables
2022-09-17 Update standby related methods
2022-09-20 Finishing the skeleton codes
2022-09-21 Fix standby_routine() and Serial guard issues
2022-09-22 Update change log and remove unnecessary comments
2022-09-23 Initiate version 2.0; Remove out-of-date codes;
2022-09-26 Test
2022-09-27 Allow global access of time keeper
2022-09-28 Initiate Version 2.1 (Beta)
2022-09-28 Wrong name in README.md
2022-09-30 Create + Update LoRa_Control
2022-10-03 More on SX1227_LoRa
2022-10-03 Change SX1278 SPI init method
2022-10-03 Add LoRa parameters
2022-10-05 Add comments to SX1278_LoRa files
2022-10-09 Add basic mode-handling functions
2022-10-09 Add LoRa message handlers + Modify event functions
2022-10-09 Modify include guards
2022-10-11 Establish SPI communication between uC & SX1278
2022-10-11 Establish one-way LoRa communication (downlink)
2022-10-11 Test the use of rx status flag
2022-10-14 Change hardware connections
2022-10-20 Add a new Serial macro
2022-10-20 Nada
2022-11-02 Version 2.1.2 (beta) - change to I2C for BME280
2022-11-10 new version: tf module
2022-11-18 Add simple test for rain gauge
2022-12-12 add descriptions
2022-12-12 Change a file's name
2022-12-25 New rain gauge test + init microSD module
2023-01-03 new idea on sd
2023-01-30 Rename repositories
2023-01-30 add STM32 end of the 3-way UART communication
2023-01-30 add bridge for 3-way UART communication
2023-02-09 some more lines; update test for microSD
2023-02-10 some changes to the structure of the card module
2023-02-11 some more for microSD card module
2023-02-27 InfluxDB from RNT
2023-02-27 Rename directories
2023-02-27 add simulations and results
2023-03-04 modify adc_DMA tests
2023-03-04 add rain gauge resolution test
2023-03-06 New prototype design + update rain gauge test
2023-03-25 Initialisation of the thesis
2023-03-25 Restructure with archives
2023-04-01 Modify microSD card access
2023-04-01 Rename files and update README
2023-04-01 Change anemometer reading method
2023-04-06 meh...
2023-04-22 Add server tests: ThingSpeak + InfluxDB
2023-04-23 Modify method(s) for anemometer
2023-04-23 Update flag-related methods
2023-04-23 Update methods for "Precipitation" module
2023-05-06 Updates for RTC and rain gauge
2023-05-15 DS18B20: timer for delay + new method
2023-05-27 New test - to be cont...
2023-07-11 New software version + new data
2023-07-11 simulation for LM317
2023-07-15 hardware update
2023-07-16 Schematic update
2023-07-16 Update PCB
2023-07-18 First version of updated board
2023-07-18 Fill modification + gerber files
2023-07-18 Finalise 2nd version
2023-10-14 All updates: codes and hardware 14 Oct
2023-10-18 Files for submission
2023-10-18 typo
2023-10-18 Introduce calibration data
2023-10-23 Moving files
